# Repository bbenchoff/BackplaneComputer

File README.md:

BackplaneComputer
=================

Design of a backplane computer

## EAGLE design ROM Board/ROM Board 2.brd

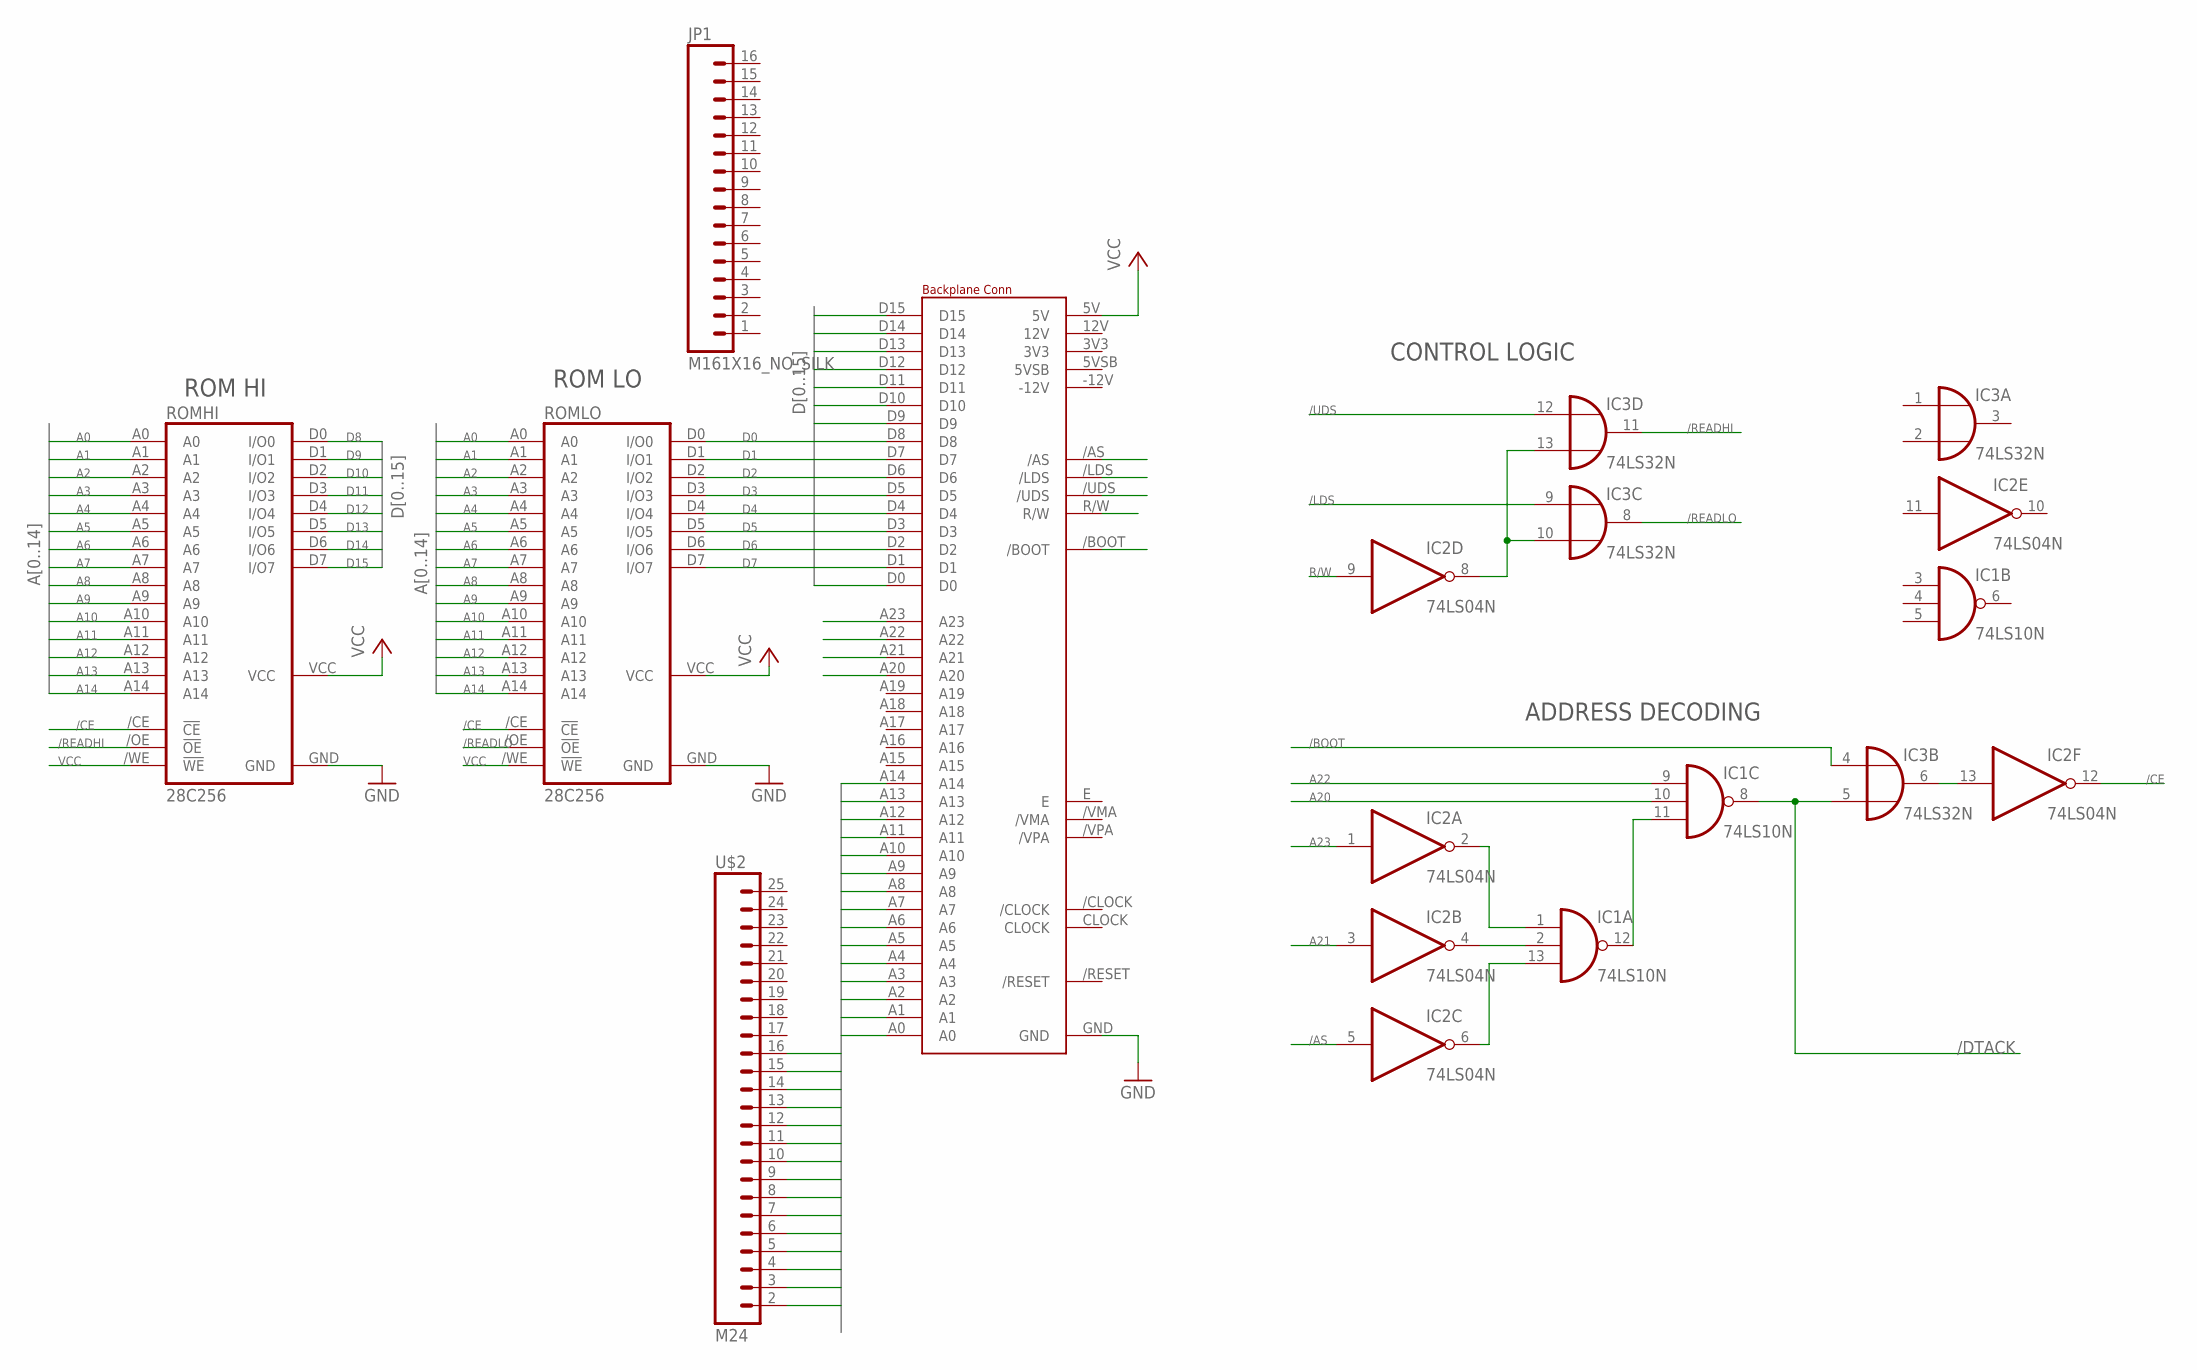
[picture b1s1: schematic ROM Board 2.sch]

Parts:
IC1: 74LS10N; DIL14
IC2: 74LS04N; DIL14
IC3: 74LS32N; DIL14
JP1: M161X16_NO_SILK; 1X16_NO_SILK
ROMHI: 28C256; DIL28-6
ROMLO: 28C256; DIL28-6
U$1: BACKPLANECONN; BLANKBOARD
U$2: M24; 1X24

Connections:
/AS: IC2.5 (I), U$1./AS
/BOOT: IC3.4 (I0), U$1./BOOT
/CE: IC2.12 (O), ROMHI./CE (!CE), ROMLO./CE (!CE)
/LDS: IC3.9 (I0), U$1./LDS
/READHI: IC3.11 (O), ROMHI./OE (!OE)
/READLO: IC3.8 (O), ROMLO./OE (!OE)
/UDS: IC3.12 (I0), U$1./UDS
A0: ROMHI.A0, ROMLO.A0, U$1.A0, U$2.2
A1: ROMHI.A1, ROMLO.A1, U$1.A1, U$2.3
A2: ROMHI.A2, ROMLO.A2, U$1.A2, U$2.4
A3: ROMHI.A3, ROMLO.A3, U$1.A3, U$2.5
A4: ROMHI.A4, ROMLO.A4, U$1.A4, U$2.6
A5: ROMHI.A5, ROMLO.A5, U$1.A5, U$2.7
A6: ROMHI.A6, ROMLO.A6, U$1.A6, U$2.8
A7: ROMHI.A7, ROMLO.A7, U$1.A7, U$2.9
A8: ROMHI.A8, ROMLO.A8, U$1.A8, U$2.10
A9: ROMHI.A9, ROMLO.A9, U$1.A9, U$2.11
A10: ROMHI.A10, ROMLO.A10, U$1.A10, U$2.12
A11: ROMHI.A11, ROMLO.A11, U$1.A11, U$2.13
A12: ROMHI.A12, ROMLO.A12, U$1.A12, U$2.14
A13: ROMHI.A13, ROMLO.A13, U$1.A13, U$2.15
A14: ROMHI.A14, ROMLO.A14, U$1.A14, U$2.16
A20: IC1.10 (I1), U$1.A20
A21: IC2.3 (I), U$1.A21
A22: IC1.9 (I0), U$1.A22
A23: IC2.1 (I), U$1.A23
D0: ROMLO.D0 (I/O0), U$1.D0
D1: ROMLO.D1 (I/O1), U$1.D1
D2: ROMLO.D2 (I/O2), U$1.D2
D3: ROMLO.D3 (I/O3), U$1.D3
D4: ROMLO.D4 (I/O4), U$1.D4
D5: ROMLO.D5 (I/O5), U$1.D5
D6: ROMLO.D6 (I/O6), U$1.D6
D7: ROMLO.D7 (I/O7), U$1.D7
D8: ROMHI.D0 (I/O0), U$1.D8
D9: ROMHI.D1 (I/O1), U$1.D9
D10: ROMHI.D2 (I/O2), U$1.D10
D11: ROMHI.D3 (I/O3), U$1.D11
D12: ROMHI.D4 (I/O4), U$1.D12
D13: ROMHI.D5 (I/O5), U$1.D13
D14: ROMHI.D6 (I/O6), U$1.D14
D15: ROMHI.D7 (I/O7), U$1.D15
DECODEOUT: IC1.8 (O), IC3.5 (I1)
GND: IC1.7 (GND), IC2.7 (GND), IC3.7 (GND), ROMHI.GND, ROMLO.GND, U$1.GND
unnamed: IC1.1 (I0), IC2.2 (O)
unnamed: IC1.2 (I1), IC2.4 (O)
unnamed: IC1.13 (I2), IC2.6 (O)
unnamed: IC1.11 (I2), IC1.12 (O)
unnamed: IC2.13 (I), IC3.6 (O)
unnamed: IC2.8 (O), IC3.10 (I1), IC3.13 (I1)
R/W: IC2.9 (I), U$1.R/W
VCC: IC1.14 (VCC), IC2.14 (VCC), IC3.14 (VCC), ROMHI./WE (!WE), ROMHI.VCC, ROMLO./WE (!WE), ROMLO.VCC, U$1.5V

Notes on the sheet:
ROM HI
ROM LO
ADDRESS DECODING
CONTROL LOGIC
/DTACK

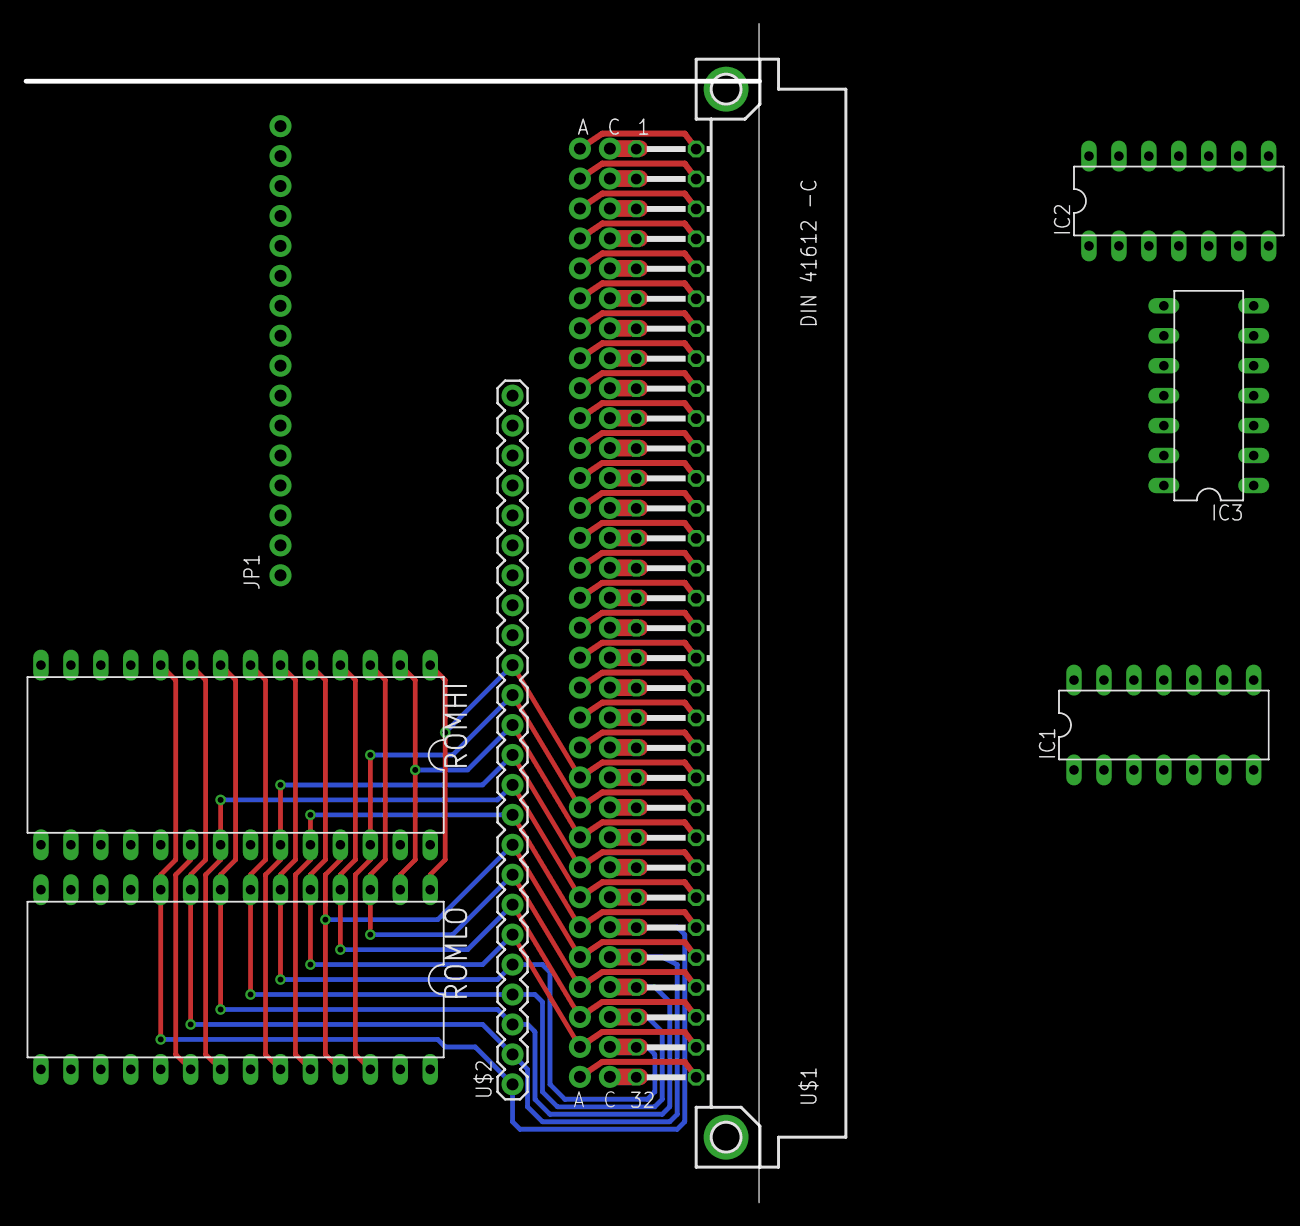
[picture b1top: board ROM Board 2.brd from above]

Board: 2 copper layers, 8 parts (0 on the bottom side), 52 nets.

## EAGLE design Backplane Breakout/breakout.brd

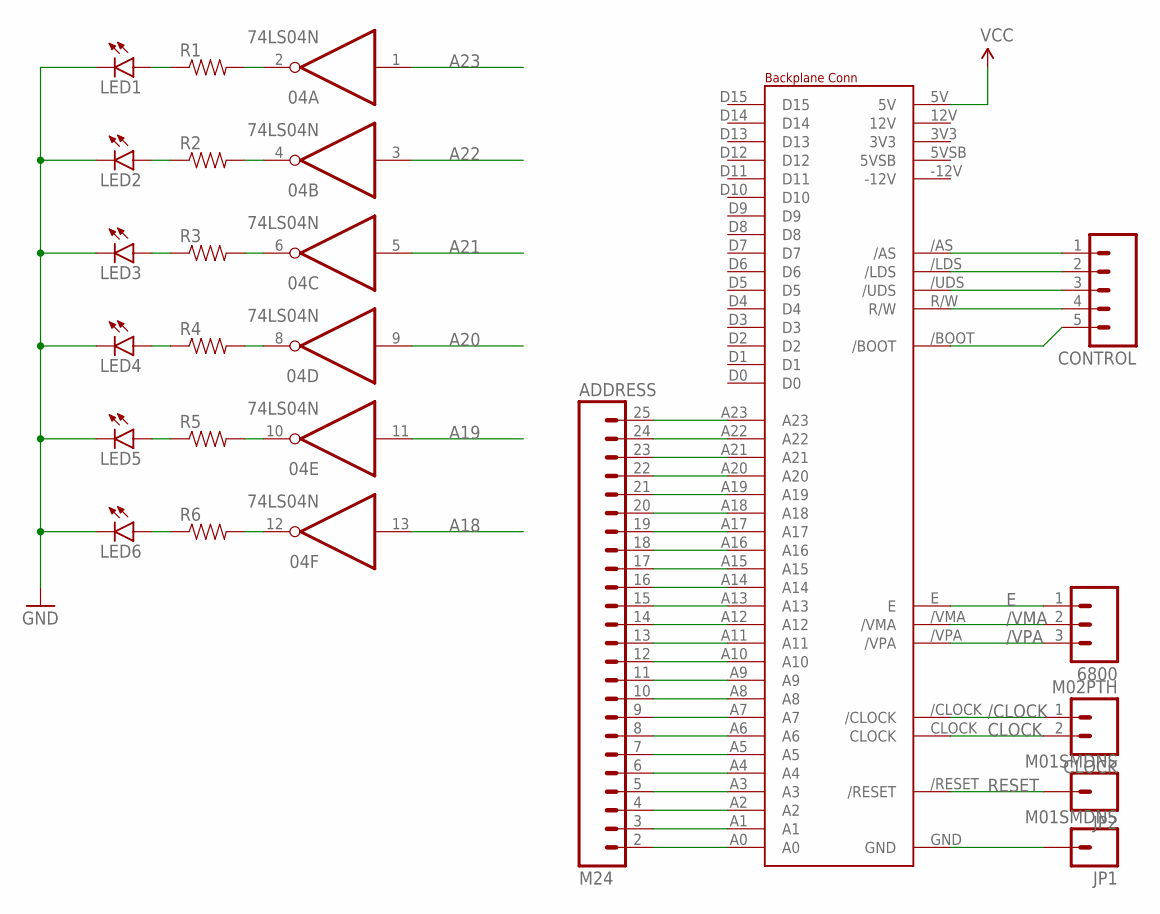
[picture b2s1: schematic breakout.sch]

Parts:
04: 74LS04N; DIL14
6800: M03PTH; 1X03
ADDRESS: M24; 1X24
CLOCK: M02PTH; 1X02
CONTROL: M05PTH; 1X05
JP1, JP2: M01SMDNS; 1X01NS
LED1, LED2, LED3, LED4, LED5, LED6: LED1206; LED-1206
R1, R2, R3, R4, R5, R6: RESISTOR0603-RES; 0603-RES
U$1: BACKPLANENOHOLES; 41612-C

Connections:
/AS: CONTROL.1, U$1./AS
/BOOT: CONTROL.5, U$1./BOOT
/CLOCK: CLOCK.1, U$1./CLOCK
/LDS: CONTROL.2, U$1./LDS
/UDS: CONTROL.3, U$1./UDS
/VMA: 6800.2, U$1./VMA
/VPA: 6800.3, U$1./VPA
A0: ADDRESS.2, U$1.A0
A1: ADDRESS.3, U$1.A1
A2: ADDRESS.4, U$1.A2
A3: ADDRESS.5, U$1.A3
A4: ADDRESS.6, U$1.A4
A5: ADDRESS.7, U$1.A5
A6: ADDRESS.8, U$1.A6
A7: ADDRESS.9, U$1.A7
A8: ADDRESS.10, U$1.A8
A9: ADDRESS.11, U$1.A9
A10: ADDRESS.12, U$1.A10
A11: ADDRESS.13, U$1.A11
A12: ADDRESS.14, U$1.A12
A13: ADDRESS.15, U$1.A13
A14: ADDRESS.16, U$1.A14
A15: ADDRESS.17, U$1.A15
A16: ADDRESS.18, U$1.A16
A17: ADDRESS.19, U$1.A17
A18: 04.13 (I), ADDRESS.20, U$1.A18
A19: 04.11 (I), ADDRESS.21, U$1.A19
A20: 04.9 (I), ADDRESS.22, U$1.A20
A21: 04.5 (I), ADDRESS.23, U$1.A21
A22: 04.3 (I), ADDRESS.24, U$1.A22
A23: 04.1 (I), ADDRESS.25, U$1.A23
CLOCK: CLOCK.2, U$1.CLOCK
E: 6800.1, U$1.E
GND: 04.7 (GND), JP1.1, LED1.C, LED2.C, LED3.C, LED4.C, LED5.C, LED6.C, U$1.GND
unnamed: 04.2 (O), R1.2
unnamed: 04.4 (O), R2.2
unnamed: 04.6 (O), R3.2
unnamed: 04.8 (O), R4.2
unnamed: 04.10 (O), R5.2
unnamed: 04.12 (O), R6.2
unnamed: LED6.A, R6.1
unnamed: LED5.A, R5.1
unnamed: LED4.A, R4.1
unnamed: LED3.A, R3.1
unnamed: LED2.A, R2.1
unnamed: LED1.A, R1.1
R/W: CONTROL.4, U$1.R/W
RESET: JP2.1, U$1./RESET
VCC: 04.14 (VCC), U$1.5V

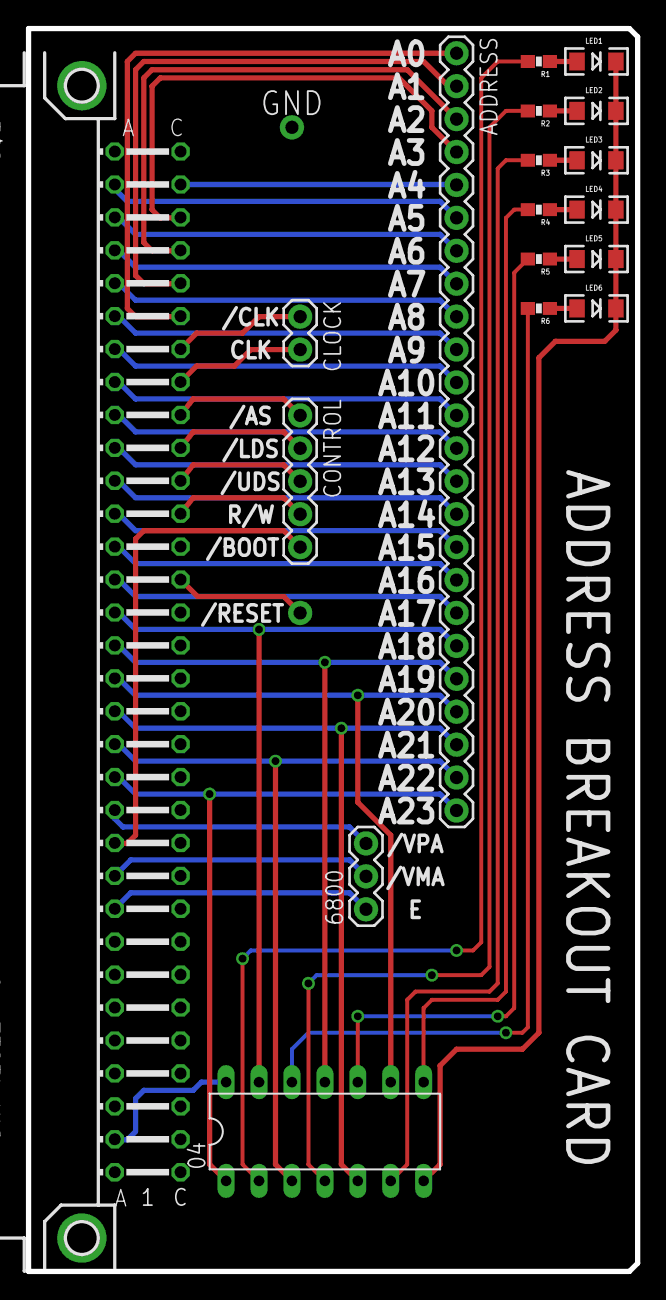
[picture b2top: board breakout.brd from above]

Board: 2 copper layers, 47.0 x 95.9 mm, 20 parts (0 on the bottom side), 49 nets.

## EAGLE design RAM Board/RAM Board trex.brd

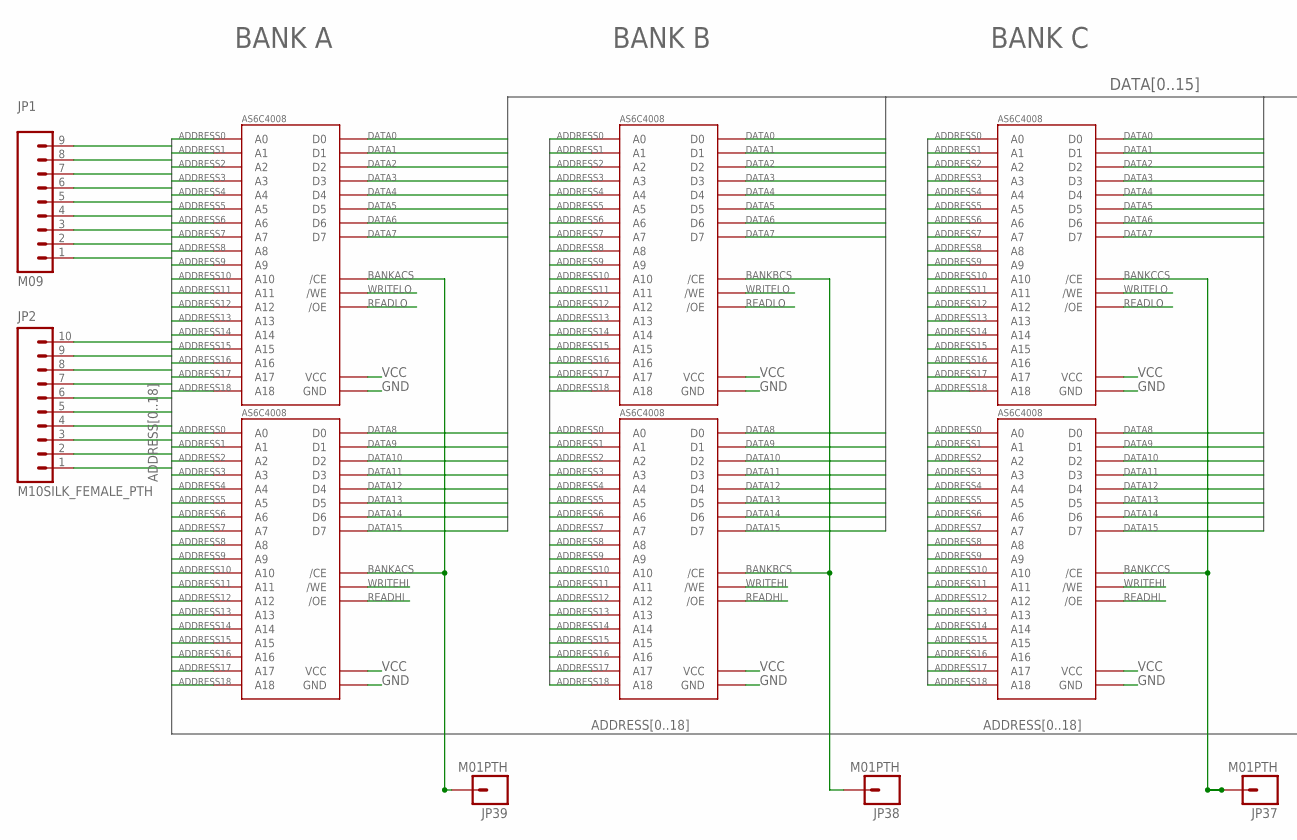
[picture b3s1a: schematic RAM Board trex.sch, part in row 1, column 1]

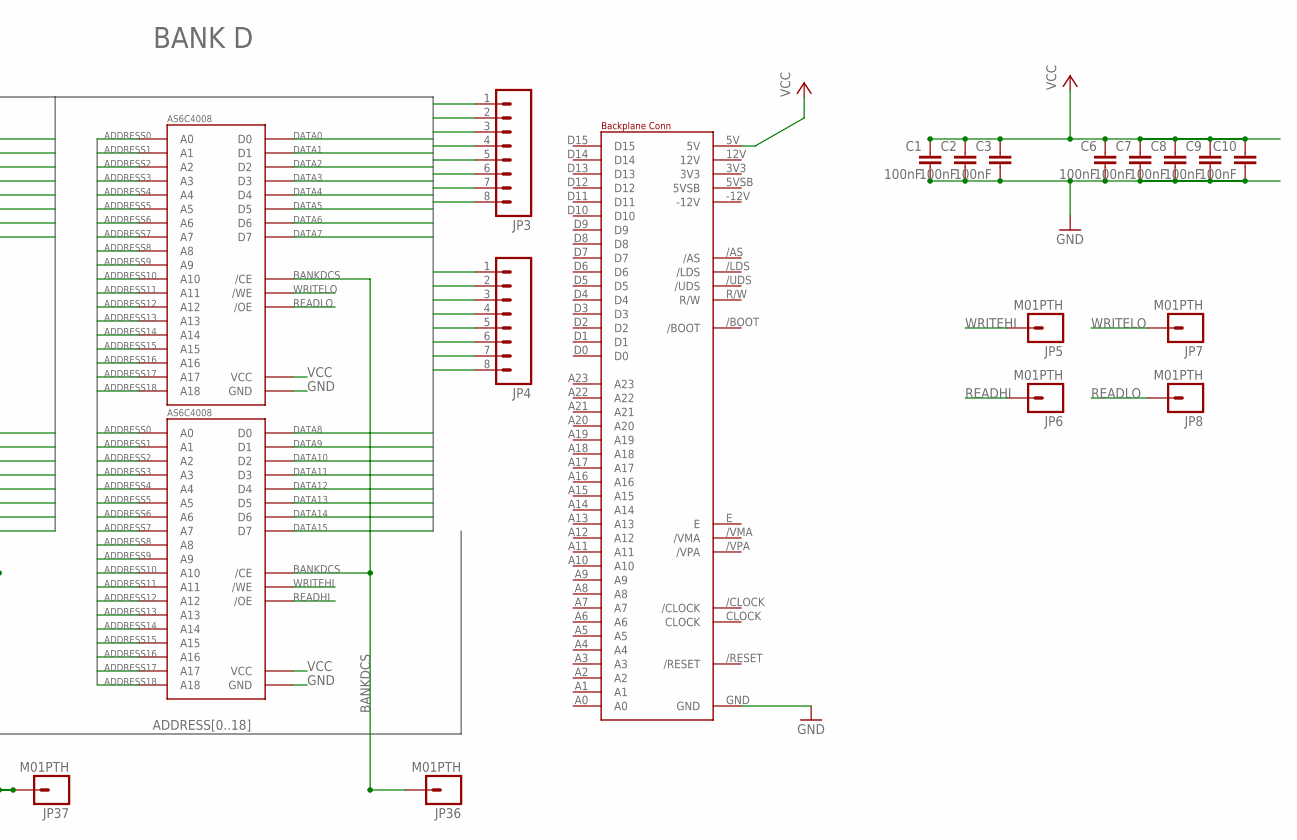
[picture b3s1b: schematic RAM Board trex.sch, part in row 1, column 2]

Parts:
AH: AS6C4008; DIL32
AL: AS6C4008; DIL32
BH: AS6C4008; DIL32
BL: AS6C4008; DIL32
C1, C2, C3, C6, C7, C8, C9, C10: 100nF; CAP-PTH-SMALL
CH: AS6C4008; DIL32
CL: AS6C4008; DIL32
DH: AS6C4008; DIL32
DL: AS6C4008; DIL32
JP1: M09; 1X09
JP2: M10SILK_FEMALE_PTH; 1X10
JP3, JP4: M08; 1X08_ROUND
JP5, JP6, JP7, JP8, JP36, JP37, JP38, JP39: M01PTH; 1X01
U$1: BACKPLANECONN; BLANKBOARD

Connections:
ADDRESS0: AH.12 (A0), AL.12 (A0), BH.12 (A0), BL.12 (A0), CH.12 (A0), CL.12 (A0), DH.12 (A0), DL.12 (A0), JP1.9
ADDRESS1: AH.11 (A1), AL.11 (A1), BH.11 (A1), BL.11 (A1), CH.11 (A1), CL.11 (A1), DH.11 (A1), DL.11 (A1), JP1.8
ADDRESS2: AH.10 (A2), AL.10 (A2), BH.10 (A2), BL.10 (A2), CH.10 (A2), CL.10 (A2), DH.10 (A2), DL.10 (A2), JP1.7
ADDRESS3: AH.9 (A3), AL.9 (A3), BH.9 (A3), BL.9 (A3), CH.9 (A3), CL.9 (A3), DH.9 (A3), DL.9 (A3), JP1.6
ADDRESS4: AH.8 (A4), AL.8 (A4), BH.8 (A4), BL.8 (A4), CH.8 (A4), CL.8 (A4), DH.8 (A4), DL.8 (A4), JP1.5
ADDRESS5: AH.7 (A5), AL.7 (A5), BH.7 (A5), BL.7 (A5), CH.7 (A5), CL.7 (A5), DH.7 (A5), DL.7 (A5), JP1.4
ADDRESS6: AH.6 (A6), AL.6 (A6), BH.6 (A6), BL.6 (A6), CH.6 (A6), CL.6 (A6), DH.6 (A6), DL.6 (A6), JP1.3
ADDRESS7: AH.5 (A7), AL.5 (A7), BH.5 (A7), BL.5 (A7), CH.5 (A7), CL.5 (A7), DH.5 (A7), DL.5 (A7), JP1.2
ADDRESS8: AH.27 (A8), AL.27 (A8), BH.27 (A8), BL.27 (A8), CH.27 (A8), CL.27 (A8), DH.27 (A8), DL.27 (A8), JP1.1
ADDRESS9: AH.26 (A9), AL.26 (A9), BH.26 (A9), BL.26 (A9), CH.26 (A9), CL.26 (A9), DH.26 (A9), DL.26 (A9), JP2.10
ADDRESS10: AH.23 (A10), AL.23 (A10), BH.23 (A10), BL.23 (A10), CH.23 (A10), CL.23 (A10), DH.23 (A10), DL.23 (A10), JP2.9
ADDRESS11: AH.25 (A11), AL.25 (A11), BH.25 (A11), BL.25 (A11), CH.25 (A11), CL.25 (A11), DH.25 (A11), DL.25 (A11), JP2.8
ADDRESS12: AH.4 (A12), AL.4 (A12), BH.4 (A12), BL.4 (A12), CH.4 (A12), CL.4 (A12), DH.4 (A12), DL.4 (A12), JP2.7
ADDRESS13: AH.28 (A13), AL.28 (A13), BH.28 (A13), BL.28 (A13), CH.28 (A13), CL.28 (A13), DH.28 (A13), DL.28 (A13), JP2.6
ADDRESS14: AH.3 (A14), AL.3 (A14), BH.3 (A14), BL.3 (A14), CH.3 (A14), CL.3 (A14), DH.3 (A14), DL.3 (A14), JP2.5
ADDRESS15: AH.31 (A15), AL.31 (A15), BH.31 (A15), BL.31 (A15), CH.31 (A15), CL.31 (A15), DH.31 (A15), DL.31 (A15), JP2.4
ADDRESS16: AH.2 (A16), AL.2 (A16), BH.2 (A16), BL.2 (A16), CH.2 (A16), CL.2 (A16), DH.2 (A16), DL.2 (A16), JP2.3
ADDRESS17: AH.30 (A17), AL.30 (A17), BH.30 (A17), BL.30 (A17), CH.30 (A17), CL.30 (A17), DH.30 (A17), DL.30 (A17), JP2.2
ADDRESS18: AH.1 (A18), AL.1 (A18), BH.1 (A18), BL.1 (A18), CH.1 (A18), CL.1 (A18), DH.1 (A18), DL.1 (A18), JP2.1
BANKACS: AH.22 (/CE), AL.22 (/CE), JP39.1
BANKBCS: BH.22 (/CE), BL.22 (/CE), JP38.1
BANKCCS: CH.22 (/CE), CL.22 (/CE), JP37.1
BANKDCS: DH.22 (/CE), DL.22 (/CE), JP36.1
DATA0: AL.13 (D0), BL.13 (D0), CL.13 (D0), DL.13 (D0), JP3.1
DATA1: AL.14 (D1), BL.14 (D1), CL.14 (D1), DL.14 (D1), JP3.2
DATA2: AL.15 (D2), BL.15 (D2), CL.15 (D2), DL.15 (D2), JP3.3
DATA3: AL.17 (D3), BL.17 (D3), CL.17 (D3), DL.17 (D3), JP3.4
DATA4: AL.18 (D4), BL.18 (D4), CL.18 (D4), DL.18 (D4), JP3.5
DATA5: AL.19 (D5), BL.19 (D5), CL.19 (D5), DL.19 (D5), JP3.6
DATA6: AL.20 (D6), BL.20 (D6), CL.20 (D6), DL.20 (D6), JP3.7
DATA7: AL.21 (D7), BL.21 (D7), CL.21 (D7), DL.21 (D7), JP3.8
DATA8: AH.13 (D0), BH.13 (D0), CH.13 (D0), DH.13 (D0), JP4.1
DATA9: AH.14 (D1), BH.14 (D1), CH.14 (D1), DH.14 (D1), JP4.2
DATA10: AH.15 (D2), BH.15 (D2), CH.15 (D2), DH.15 (D2), JP4.3
DATA11: AH.17 (D3), BH.17 (D3), CH.17 (D3), DH.17 (D3), JP4.4
DATA12: AH.18 (D4), BH.18 (D4), CH.18 (D4), DH.18 (D4), JP4.5
DATA13: AH.19 (D5), BH.19 (D5), CH.19 (D5), DH.19 (D5), JP4.6
DATA14: AH.20 (D6), BH.20 (D6), CH.20 (D6), DH.20 (D6), JP4.7
DATA15: AH.21 (D7), BH.21 (D7), CH.21 (D7), DH.21 (D7), JP4.8
GND: AH.16 (GND), AL.16 (GND), BH.16 (GND), BL.16 (GND), C1.2, C2.2, C3.2, C6.2, C7.2, C8.2, C9.2, C10.2, CH.16 (GND), CL.16 (GND), DH.16 (GND), DL.16 (GND), U$1.GND
READHI: AH.24 (/OE), BH.24 (/OE), CH.24 (/OE), DH.24 (/OE), JP6.1
READLO: AL.24 (/OE), BL.24 (/OE), CL.24 (/OE), DL.24 (/OE), JP8.1
VCC: AH.32 (VCC), AL.32 (VCC), BH.32 (VCC), BL.32 (VCC), C1.1, C2.1, C3.1, C6.1, C7.1, C8.1, C9.1, C10.1, CH.32 (VCC), CL.32 (VCC), DH.32 (VCC), DL.32 (VCC), U$1.5V
WRITEHI: AH.29 (/WE), BH.29 (/WE), CH.29 (/WE), DH.29 (/WE), JP5.1
WRITELO: AL.29 (/WE), BL.29 (/WE), CL.29 (/WE), DL.29 (/WE), JP7.1

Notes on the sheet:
BANK A
BANK B
BANK C
BANK D

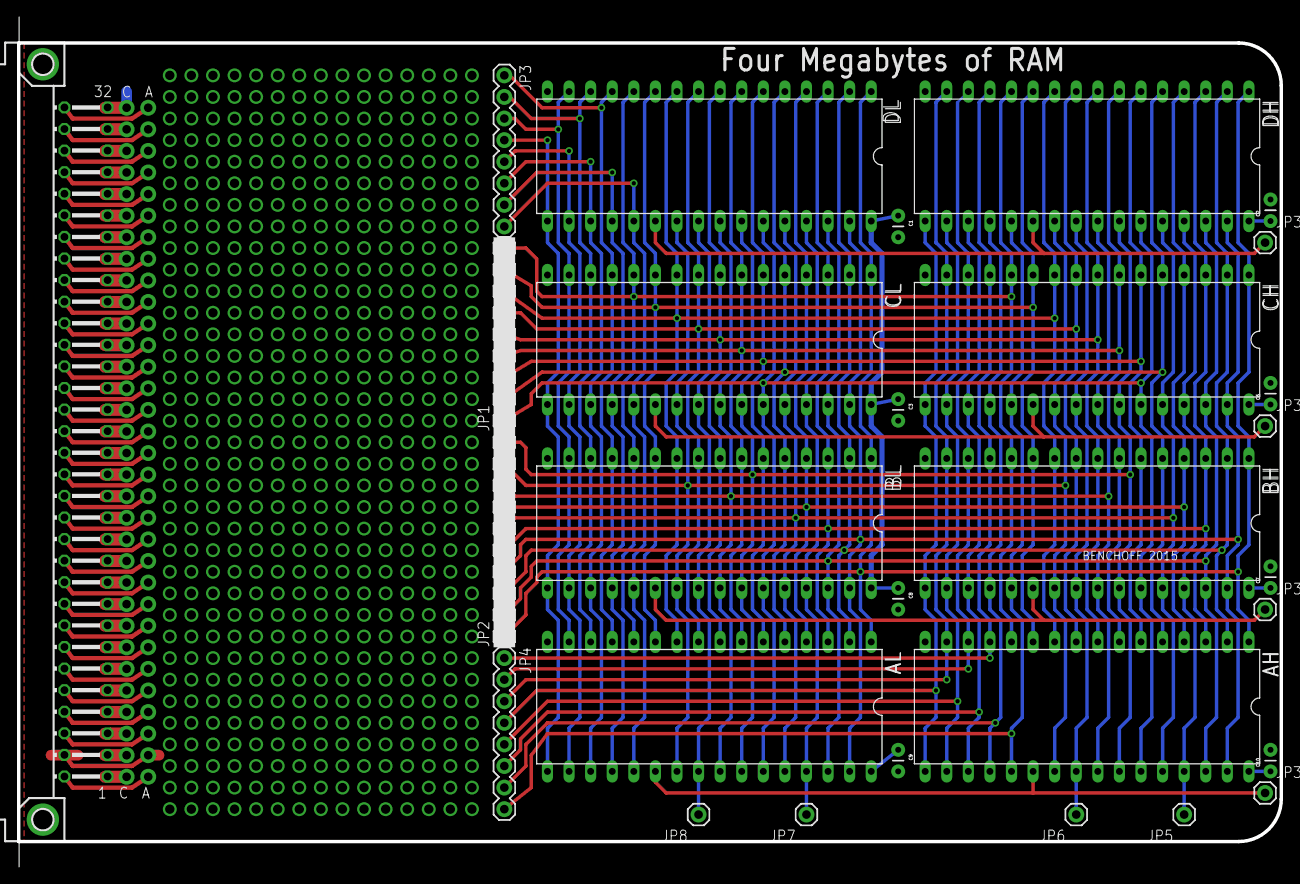
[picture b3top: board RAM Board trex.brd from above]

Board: 2 copper layers, 148.6 x 100.0 mm, 29 parts (0 on the bottom side), 45 nets.

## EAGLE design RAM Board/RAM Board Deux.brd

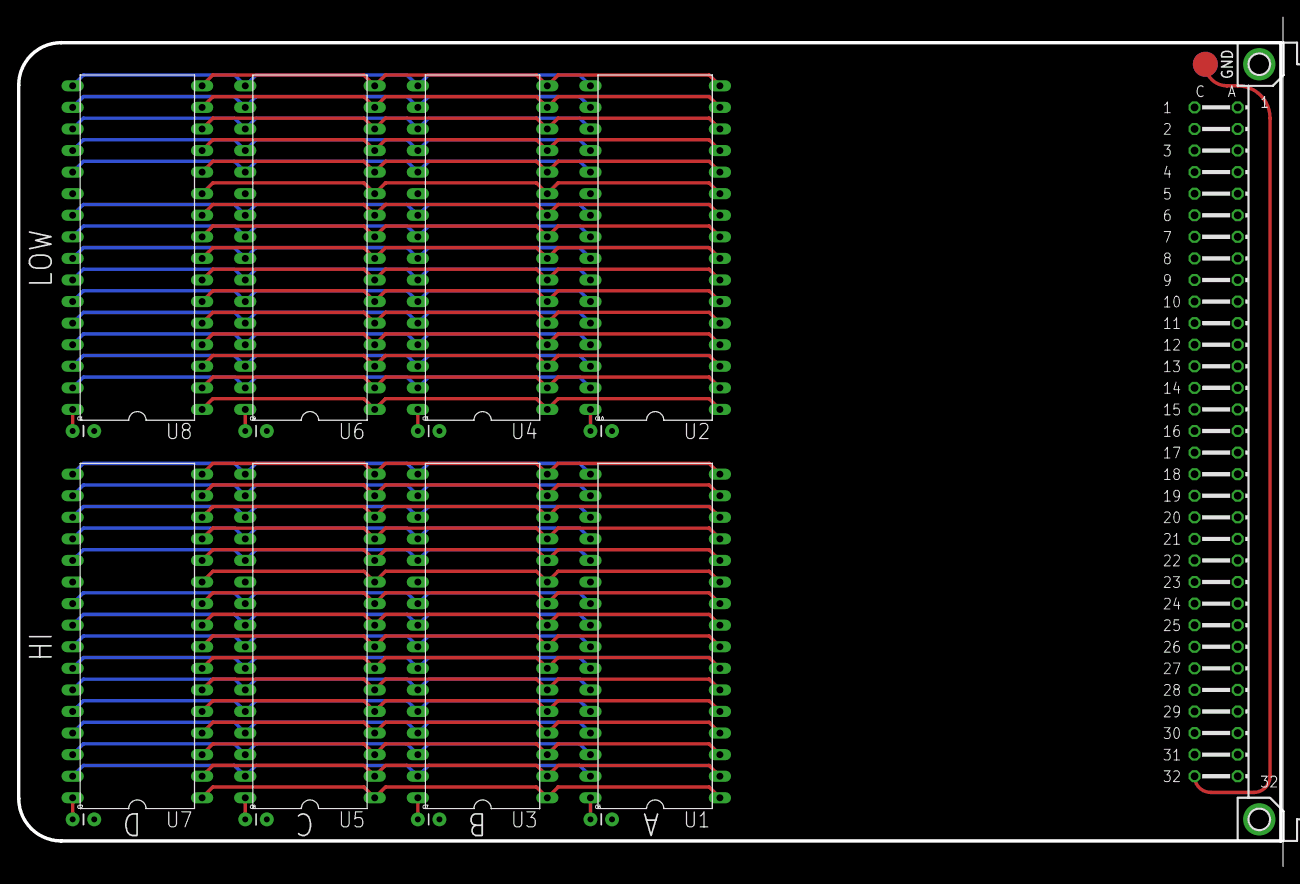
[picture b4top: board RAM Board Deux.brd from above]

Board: 2 copper layers, 148.8 x 100.0 mm, 17 parts (0 on the bottom side), 46 nets.

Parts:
C1, C2, C3, C6, C7, C8, C9, C10: 100nF; CAP-PTH-SMALL
U1, U2, U3, U4, U5, U6, U7, U8: AS6C4008; DIL32
U$1: BLANKBOARD

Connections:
ADDRESS0: U1.12, U2.12, U3.12, U4.12, U5.12, U6.12, U7.12, U8.12
ADDRESS1: U1.11, U2.11, U3.11, U4.11, U5.11, U6.11, U7.11, U8.11
ADDRESS2: U1.10, U2.10, U3.10, U4.10, U5.10, U6.10, U7.10, U8.10
ADDRESS3: U1.9, U2.9, U3.9, U4.9, U5.9, U6.9, U7.9, U8.9
ADDRESS4: U1.8, U2.8, U3.8, U4.8, U5.8, U6.8, U7.8, U8.8
ADDRESS5: U1.7, U2.7, U3.7, U4.7, U5.7, U6.7, U7.7, U8.7
ADDRESS6: U1.6, U2.6, U3.6, U4.6, U5.6, U6.6, U7.6, U8.6
ADDRESS7: U1.5, U2.5, U3.5, U4.5, U5.5, U6.5, U7.5, U8.5
ADDRESS8: U1.27, U2.27, U3.27, U4.27, U5.27, U6.27, U7.27, U8.27
ADDRESS9: U1.26, U2.26, U3.26, U4.26, U5.26, U6.26, U7.26, U8.26
ADDRESS10: U1.23, U2.23, U3.23, U4.23, U5.23, U6.23, U7.23, U8.23
ADDRESS11: U1.25, U2.25, U3.25, U4.25, U5.25, U6.25, U7.25, U8.25
ADDRESS12: U1.4, U2.4, U3.4, U4.4, U5.4, U6.4, U7.4, U8.4
ADDRESS13: U1.28, U2.28, U3.28, U4.28, U5.28, U6.28, U7.28, U8.28
ADDRESS14: U1.3, U2.3, U3.3, U4.3, U5.3, U6.3, U7.3, U8.3
ADDRESS15: U1.31, U2.31, U3.31, U4.31, U5.31, U6.31, U7.31, U8.31
ADDRESS16: U1.2, U2.2, U3.2, U4.2, U5.2, U6.2, U7.2, U8.2
ADDRESS17: U1.30, U2.30, U3.30, U4.30, U5.30, U6.30, U7.30, U8.30
ADDRESS18: U1.1, U2.1, U3.1, U4.1, U5.1, U6.1, U7.1, U8.1
BANKACS: U1.22, U2.22
BANKBCS: U3.22, U4.22
BANKCCS: U5.22, U6.22
BANKDCS: U7.22, U8.22
DATA0: U2.13, U4.13, U6.13, U8.13
DATA1: U2.14, U4.14, U6.14, U8.14
DATA2: U2.15, U4.15, U6.15, U8.15
DATA3: U2.17, U4.17, U6.17, U8.17
DATA4: U2.18, U4.18, U6.18, U8.18
DATA5: U2.19, U4.19, U6.19, U8.19
DATA6: U2.20, U4.20, U6.20, U8.20
DATA7: U2.21, U4.21, U6.21, U8.21
DATA8: U1.13, U3.13, U5.13, U7.13
DATA9: U1.14, U3.14, U5.14, U7.14
DATA10: U1.15, U3.15, U5.15, U7.15
DATA11: U1.17, U3.17, U5.17, U7.17
DATA12: U1.18, U3.18, U5.18, U7.18
DATA13: U1.19, U3.19, U5.19, U7.19
DATA14: U1.20, U3.20, U5.20, U7.20
DATA15: U1.21, U3.21, U5.21, U7.21
GND: C1.2, C2.2, C3.2, C6.2, C7.2, C8.2, C9.2, C10.2, U1.16, U2.16, U3.16, U4.16, U5.16, U6.16, U7.16, U8.16
READHI: U1.24, U3.24, U5.24, U7.24
READLO: U2.24, U4.24, U6.24, U8.24
S$1: C2.1, U7.32
VCC: C1.1, C3.1, C6.1, C7.1, C8.1, C9.1, C10.1, U1.32, U2.32, U3.32, U4.32, U5.32, U6.32, U8.32
WRITEHI: U1.29, U3.29, U5.29, U7.29
WRITELO: U2.29, U4.29, U6.29, U8.29

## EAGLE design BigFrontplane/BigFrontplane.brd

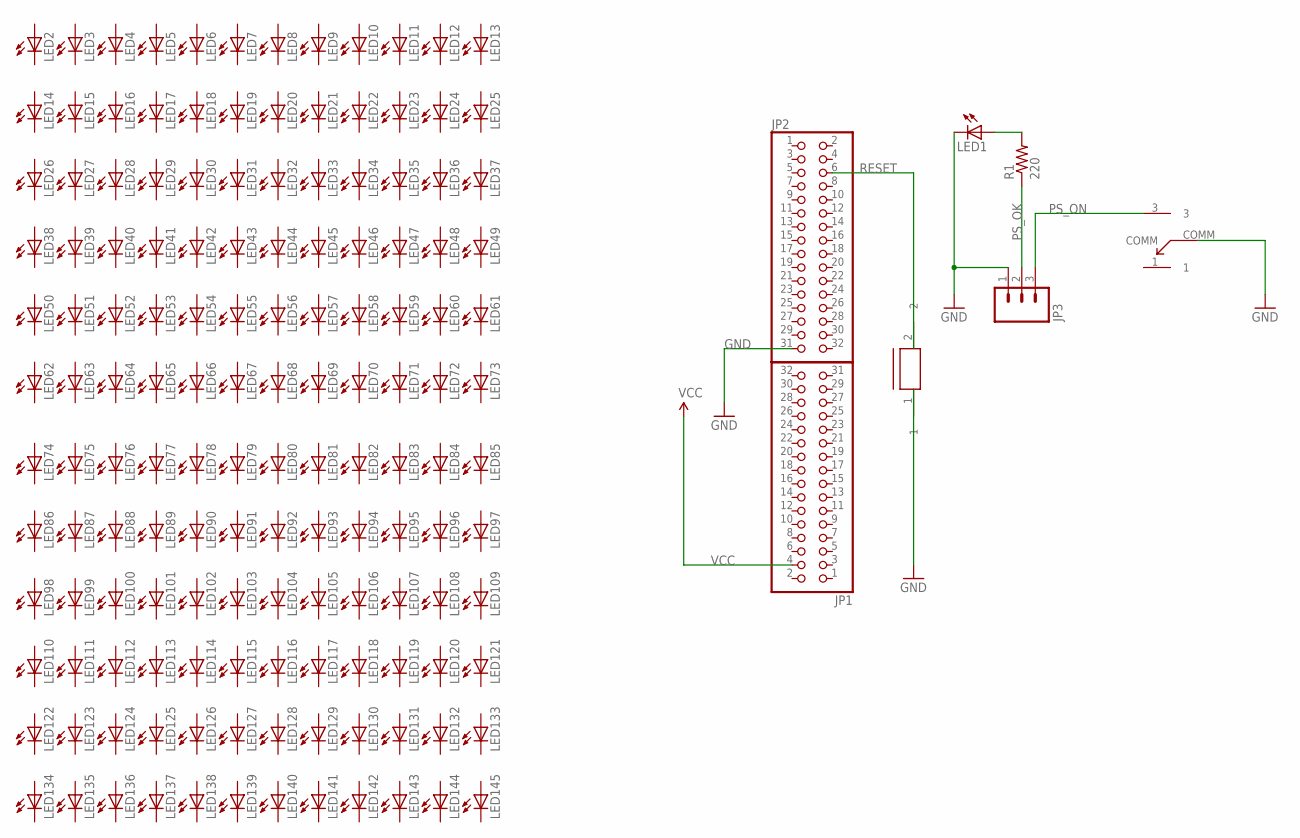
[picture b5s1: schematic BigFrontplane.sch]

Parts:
JP1, JP2: PINHD-2X16; 2X16
JP3: M03LONGPADS; 1X03_LONGPADS
LED1: LED5MM
LED2, LED3, LED4, LED5, LED6, LED7, LED8, LED9, LED10, LED11, LED12, LED13, LED14, LED15, LED16, LED17, LED18, LED19, LED20, LED21, LED22, LED23, LED24, LED25, LED26, LED27, LED28, LED29, LED30, LED31, LED32, LED33, LED34, LED35, LED36, LED37, LED38, LED39, LED40, LED41, LED42, LED43, LED44, LED45, LED46, LED47, LED48, LED49, LED50, LED51, LED52, LED53, LED54, LED55, LED56, LED57, LED58, LED59, LED60, LED61, LED62, LED63, LED64, LED65, LED66, LED67, LED68, LED69, LED70, LED71, LED72, LED73, LED74, LED75, LED76, LED77, LED78, LED79, LED80, LED81, LED82, LED83, LED84, LED85, LED86, LED87, LED88, LED89, LED90, LED91, LED92, LED93, LED94, LED95, LED96, LED97, LED98, LED99, LED100, LED101, LED102, LED103, LED104, LED105, LED106, LED107, LED108, LED109, LED110, LED111, LED112, LED113, LED114, LED115, LED116, LED117, LED118, LED119, LED120, LED121, LED122, LED123, LED124, LED125, LED126, LED127, LED128, LED129, LED130, LED131, LED132, LED133, LED134, LED135, LED136, LED137, LED138, LED139, LED140, LED141, LED142, LED143, LED144, LED145: LED3MM
R1: 220; AXIAL-0.3-KIT
U$1: 7101; 7101SYCQE
U$2: TP11

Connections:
GND: JP2.31, JP3.1, LED1.K (C), U$1.COMM, U$2.1
unnamed: LED1.A, R1.P$2 (2)
PS_OK: JP3.2, R1.P$1 (1)
PS_ON: JP3.3, U$1.3
RESET: JP2.6, U$2.2
VCC: JP1.4

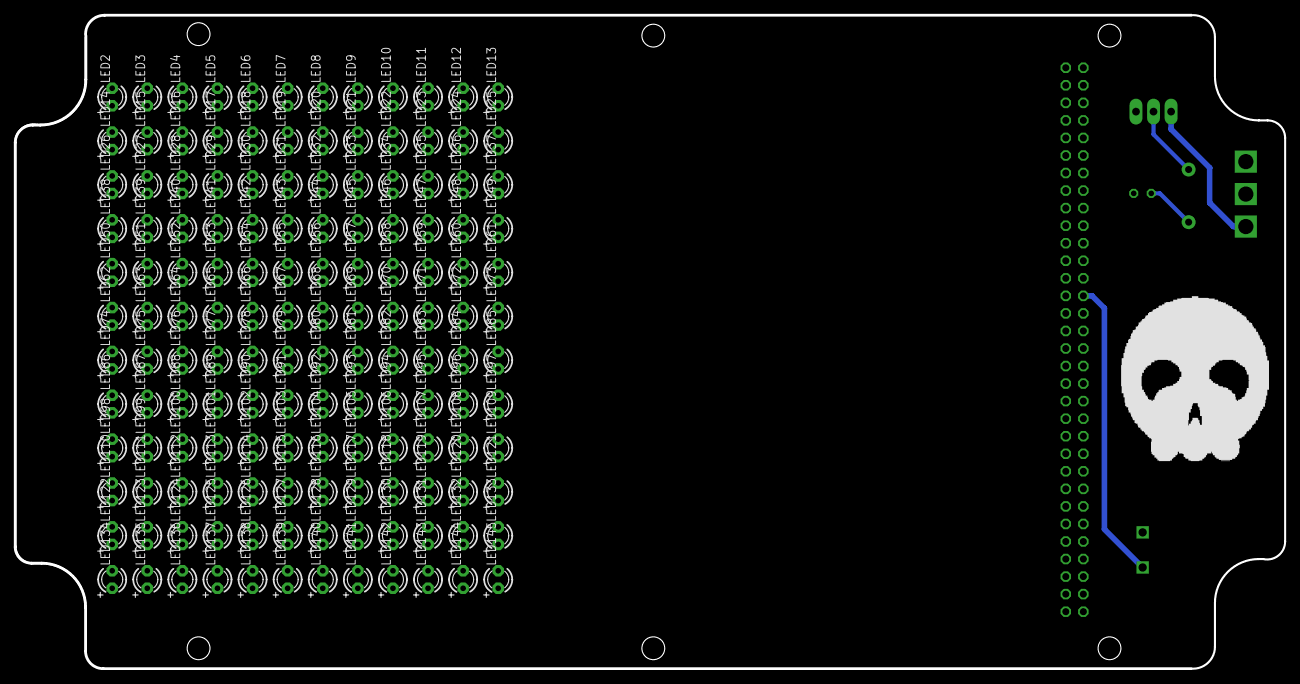
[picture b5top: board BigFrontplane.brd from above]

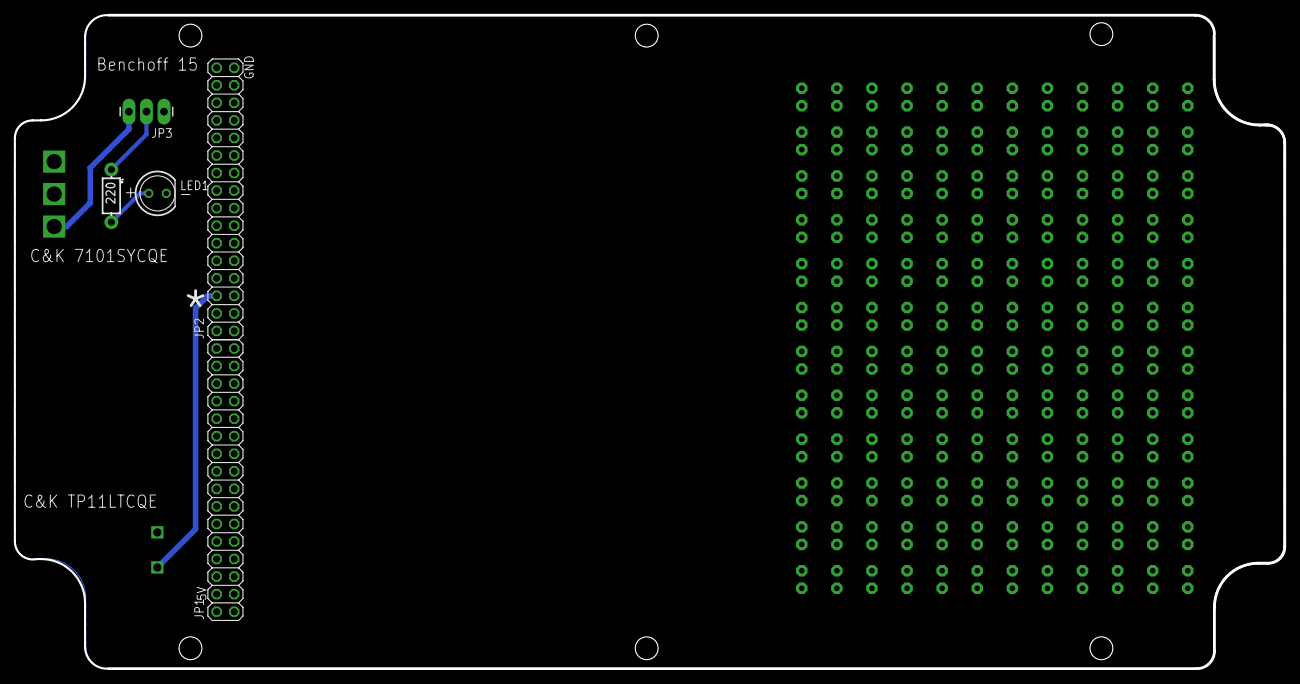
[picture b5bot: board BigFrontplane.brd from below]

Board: 2 copper layers, 183.8 x 94.6 mm, 157 parts (13 on the bottom side), 5 nets.

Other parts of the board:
U$3, U$4, U$7, U$8, U$9, U$10: STAND-OFF

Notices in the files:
parts and their libraries:
SparkFun-Connectors: Licensing: Creative Commons ShareAlike 4.0 International - https://creativecommons.org/licenses/by-sa/4.0
SparkFun-Connectors: Licensing: CC v3.0 Share-Alike You are welcome to use this library for commercial purposes.
